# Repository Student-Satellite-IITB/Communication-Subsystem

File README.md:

# Communication-Subsystem
This repository contains all codes related to the Communication Subsystem for IITBSSP CubeSat Mission

Current status: 
- Literature Review
- Link Budget Analysis

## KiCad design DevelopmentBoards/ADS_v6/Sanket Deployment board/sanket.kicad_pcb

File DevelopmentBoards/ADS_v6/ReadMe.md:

# This is work in progress

This folder contains files related to the ADS.

ADS consists of two parts:
1. Sanket Deployment Board
2. Resistor Board

The Sanket Deployment Board contains the files of the main board which houses the regulators for heating nichrome. The Resistor board is a small vertical board that holds the nichrome wires and detector switches.

# Changes in v6 over v5
- The burnwires are in series now to prevent excess current
- The R6 can connect the EN to the voltage regulator directly, enabling easy bypassing of the current limiter

# Errata
- The R12 of the Deployment board (ILIM resistor) should be around 90 kOhm.

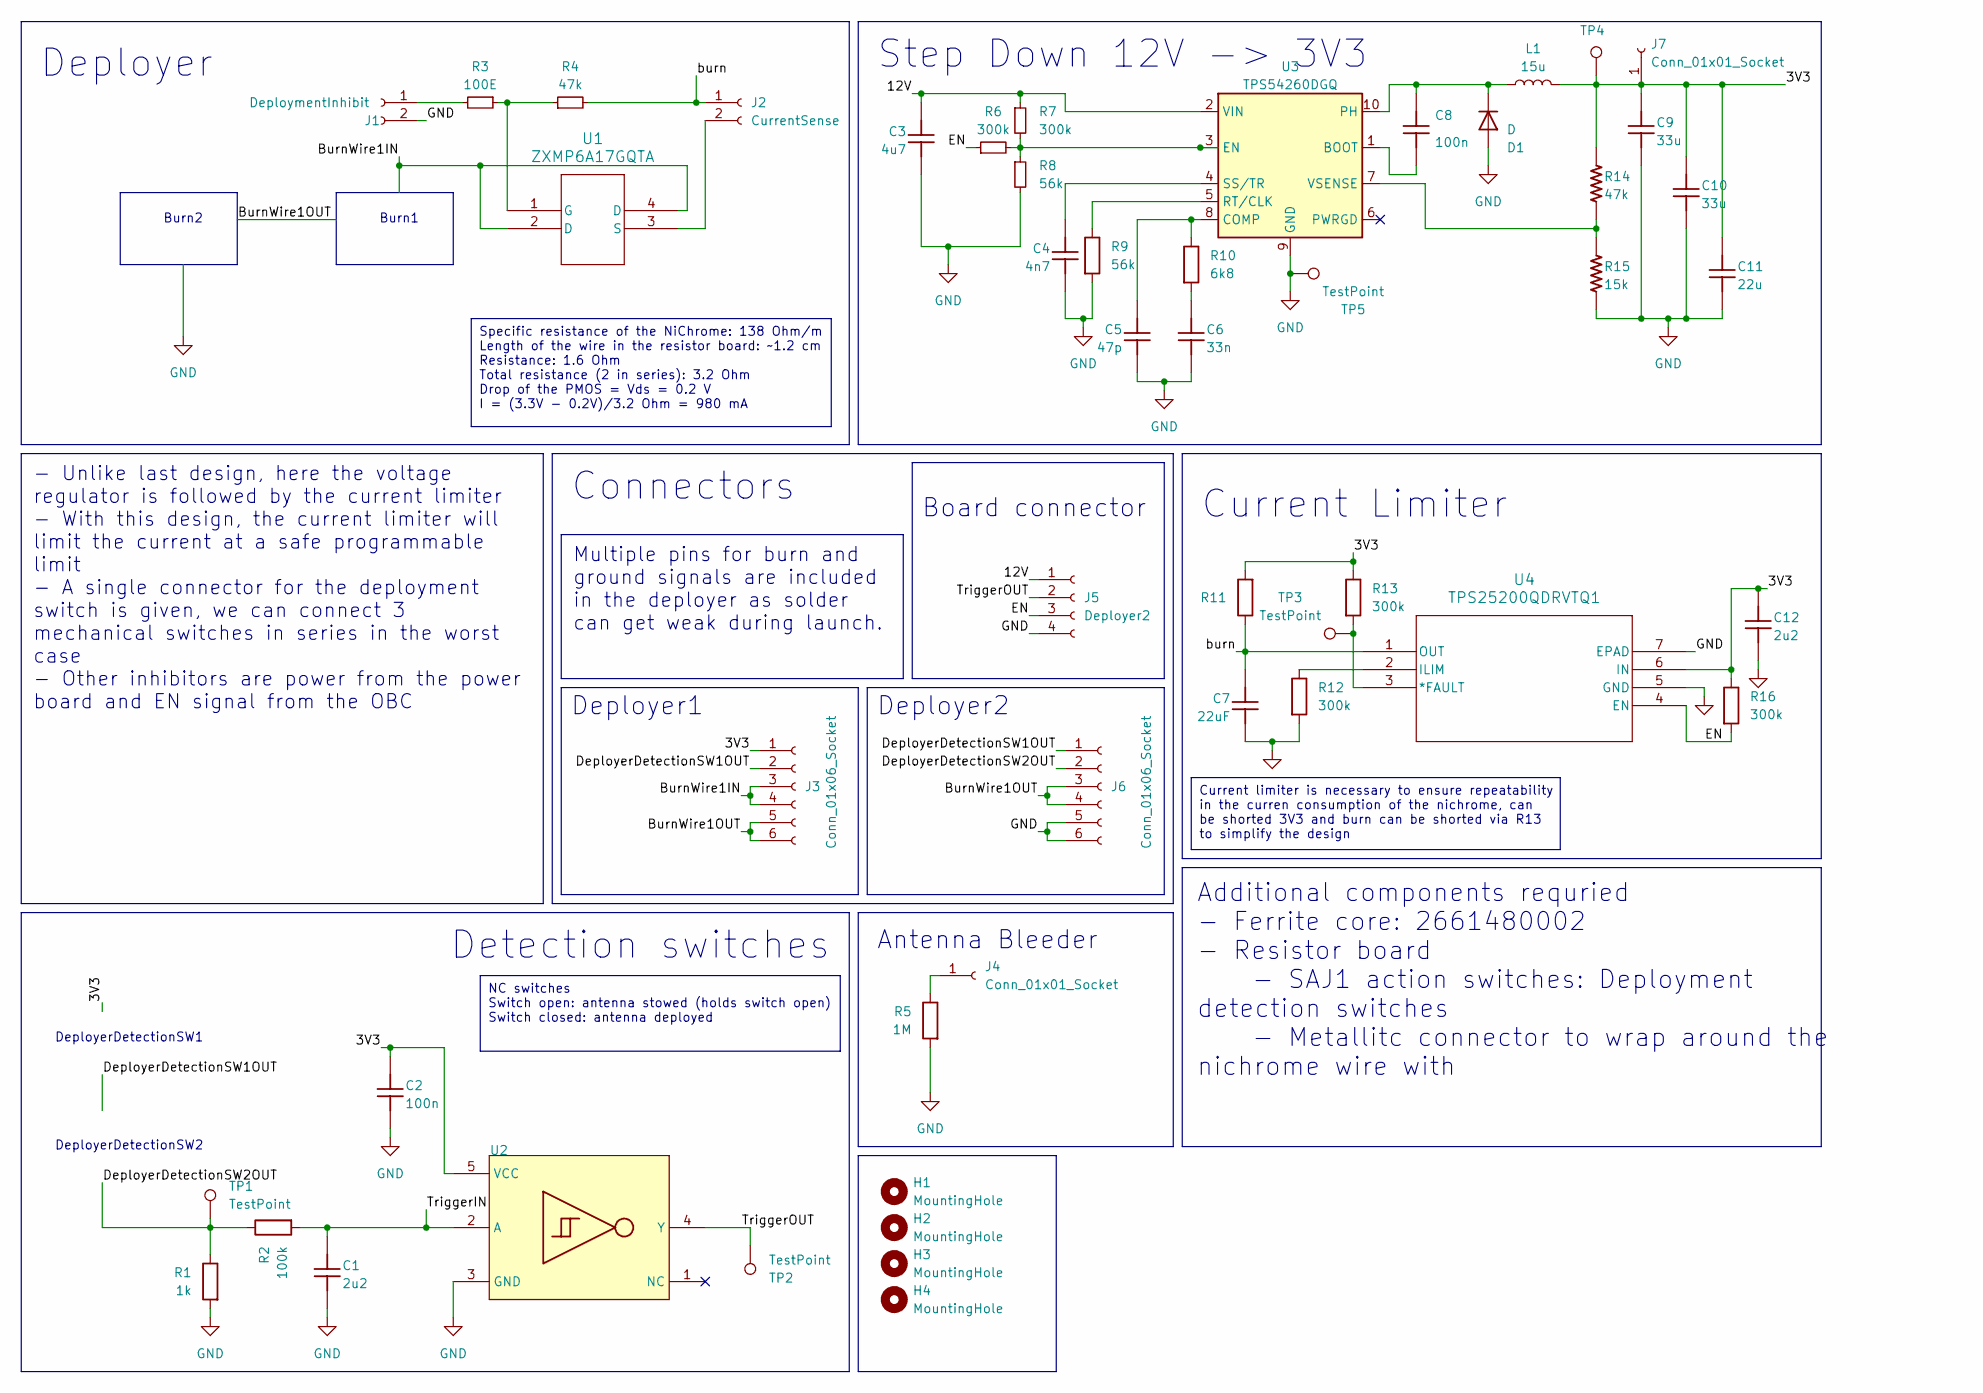
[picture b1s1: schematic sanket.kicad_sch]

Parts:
C1, C12: 2u2; C_0805_2012Metric
C2: 100n; C_0805_2012Metric
C3: 4u7; C_0805_2012Metric; MANUFACTURER PART NUMBER C0603C475K8PACTU
C4: 4n7; C_0805_2012Metric; MANUFACTURER PART NUMBER C0603C475K8PACTU
C5: 47p; C_0805_2012Metric; MANUFACTURER PART NUMBER C0603C475K8PACTU
C6: 33n; C_0805_2012Metric; MANUFACTURER PART NUMBER C0603C475K8PACTU
C7: 22uF; C_0805_2012Metric
C8: 100n; C_0805_2012Metric; MANUFACTURER PART NUMBER C0603C475K8PACTU
C9, C10: 33u; C_1206_3216Metric; MANUFACTURER PART NUMBER C0603C475K8PACTU
C11: 22u; C_0805_2012Metric; MANUFACTURER PART NUMBER C0603C475K8PACTU
D1: D; D_SMA-SMB_Universal_Handsoldering
H1, H2, H3, H4: MountingHole; MountingHole_3.2mm_M3
J1: DeploymentInhibit; PinHeader_1x02_P2.54mm_Vertical
J2: CurrentSense; PinHeader_1x02_P2.54mm_Vertical
J3, J6: Conn_01x06_Socket; PinHeader_1x06_P2.54mm_Vertical
J4, J7: Conn_01x01_Socket; PinSocket_1x01_P2.54mm_Vertical
J5: Deployer2; PinHeader_1x04_P2.54mm_Vertical
L1: 15u; L_Wurth_WE-XHMI-5050
R1: 1k; R_0805_2012Metric
R2: 100k; R_0805_2012Metric
R3: 100E; C_0805_2012Metric
R4, R14: 47k; C_0805_2012Metric
R5: 1M; R_0805_2012Metric
R6, R7: 300k; C_0805_2012Metric
R8: 56k; C_0805_2012Metric
R9: 56k; R_0805_2012Metric
R10: 6k8; R_0805_2012Metric
R11: 300k; C_0603_1608Metric
R12, R13, R16: 300k; R_0805_2012Metric
R15: 15k; C_0805_2012Metric
TP1, TP2, TP3, TP4, TP5: TestPoint; TestPoint_THTPad_1.0x1.0mm_Drill0.5mm
U1: ZXMP6A17GQTA; SOT-223_DIO
U2: SN74LVC1G17QDCKRQ1; SOT-353_SC-70-5
U3: TPS54260DGQ; HVSSOP-10-1EP_3x3mm_P0.5mm_EP1.57x1.88mm
U4: TPS25200QDRVTQ1; WSON-6-1EP_2x2mm_P0.65mm_EP1x1.6mm

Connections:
/3V3: C2.2, C9.2, C10.2, C11.2, C12.2, J3.1, J7.1, L1.2, R11.2, R13.1, R14.1, R16.1, TP4.1, U2.5 (VCC), U4.6 (IN)
/12V: C3.2, J5.1, R7.1, U3.2 (VIN)
/BurnWire1IN: J3.3, J3.4, U1.2 (D), U1.4 (D)
/BurnWire1OUT: J3.5, J3.6, J6.3, J6.4
/DeployerDetectionSW1OUT: J3.2, J6.1
/DeployerDetectionSW2OUT: J6.2, R1.1, R2.1, TP1.1
/EN: J5.3, R6.1, R16.2, U4.4 (EN)
/TriggerIN: C1.2, R2.2, U2.2 (A)
/TriggerOUT: J5.2, TP2.1, U2.4 (Y)
/burn: C7.2, J2.1, R4.2, R11.1, U4.1 (OUT)
GND: C1.1, C2.1, C3.1, C4.1, C5.1, C6.1, C7.1, C9.1, C10.1, C11.1, C12.1, D1.2 (A), J1.2, J5.4, J6.5, J6.6, R1.2, R5.2, R8.2, R9.2, R12.2, R15.2, TP5.1, U2.3 (GND), U3.9 (GND), U3.11 (GND), U4.5 (GND), U4.7 (EPAD)
unnamed: C6.2, R10.2
unnamed: C8.2, D1.1 (K), L1.1, U3.10 (PH)
unnamed: J1.1, R3.2
unnamed: J2.2, U1.3 (S)
unnamed: J4.1, R5.1
unnamed: R3.1, R4.1, U1.1 (G)
unnamed: C8.1, U3.1 (BOOT)
unnamed: C5.2, R10.1, U3.8 (COMP)
unnamed: R6.2, R7.2, R8.1, U3.3 (EN)
unnamed: R9.1, U3.5 (RT/CLK)
unnamed: C4.2, U3.4 (SS/TR)
unnamed: R14.2, R15.1, U3.7 (VSENSE)
unnamed: R13.2, TP3.1, U4.3 (*FAULT)
unnamed: R12.1, U4.2 (ILIM)

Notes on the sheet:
Multiple pins for burn and ground signals are included in the deployer as solder can get weak during launch.
NC switches Switch open: antenna stowed (holds switch open) Switch closed: antenna deployed
- Unlike last design, here the voltage regulator is followed by the current limiter - With this design, the current limiter will limit the current at a safe programmable limit - A single connector for the deployment switch is given, we can connect 3 mechanical switches in series in the worst case -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
Additional components requried - Ferrite core: 2661480002 - Resistor board - SAJ1 action switches: Deployment detection switches - Metallitc connector to wrap around the nichrome wire with
Current limiter is necessary to ensure repeatability in the curren consumption of the nichrome, can be shorted 3V3 and burn can be shorted via R13 to simplify the design
Specific resistance of the NiChrome: 138 Ohm/m Length of the wire in the resistor board: ~1.2 cm Resistance: 1.6 Ohm Total resistance (2 in series): 3.2 Ohm Drop of the PMOS = Vds = 0.2 V I = (3.3V - 0.2V)/3.2 Ohm = 980 mA
Step Down 12V -> 3V3
Detection switches
Connectors
Board connector
Deployer
Burn1
DeployerDetectionSW1
Deployer2
Current Limiter
Deployer1
DeployerDetectionSW2
Burn2
Antenna Bleeder

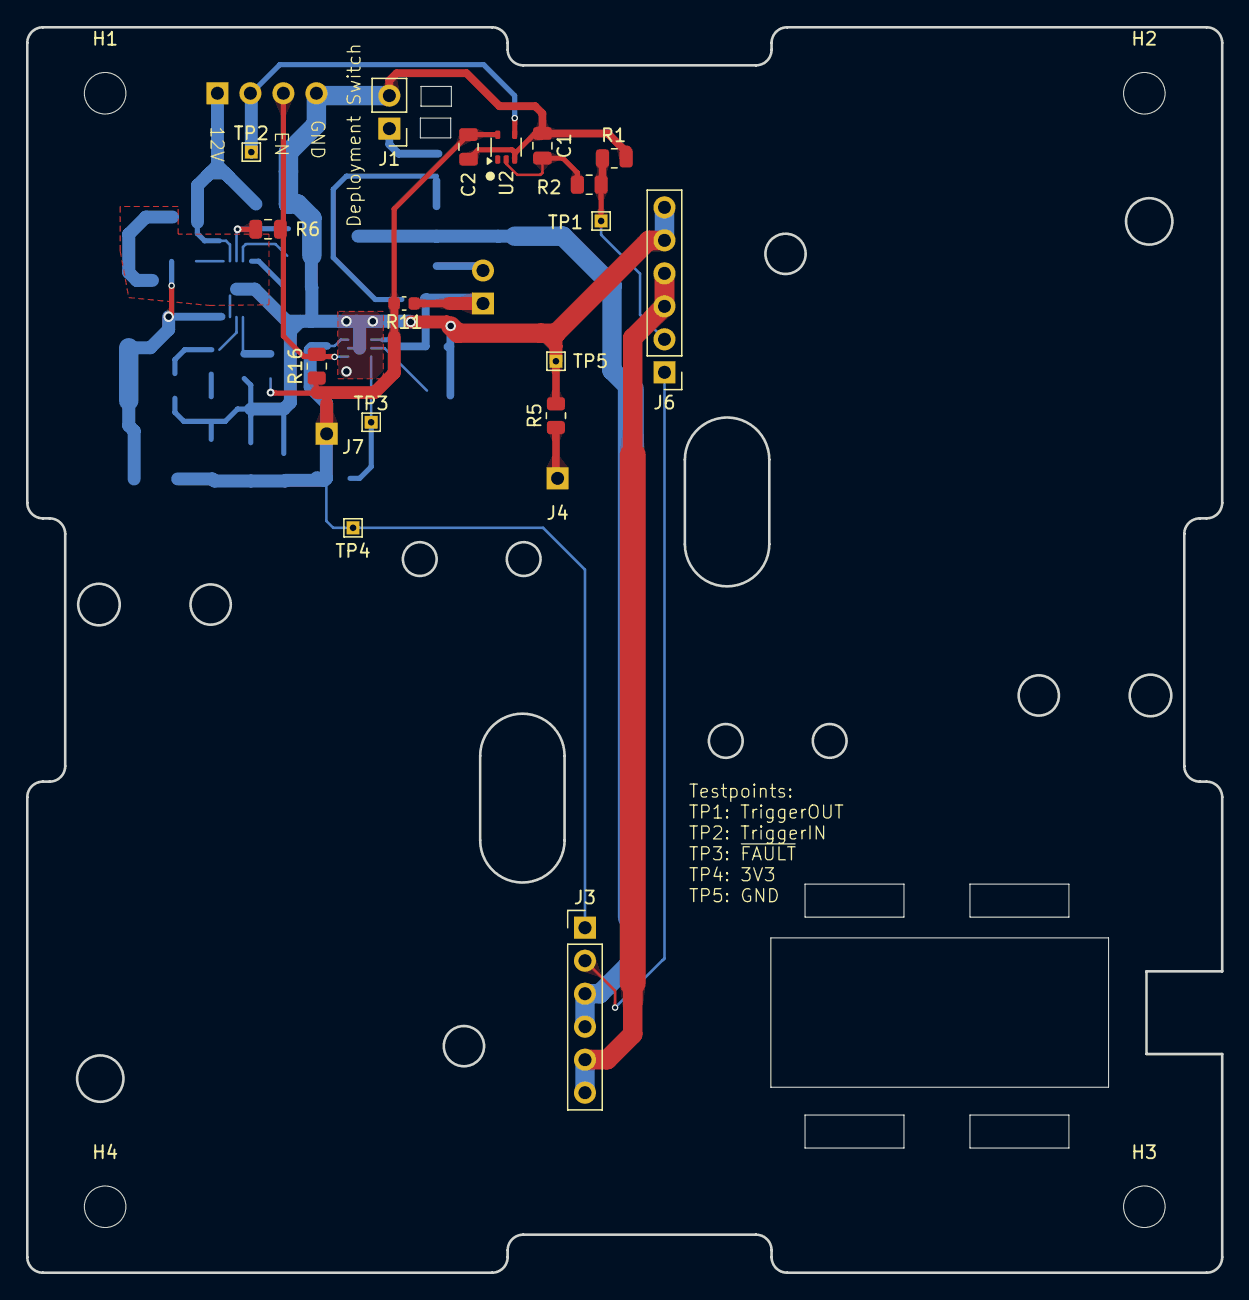
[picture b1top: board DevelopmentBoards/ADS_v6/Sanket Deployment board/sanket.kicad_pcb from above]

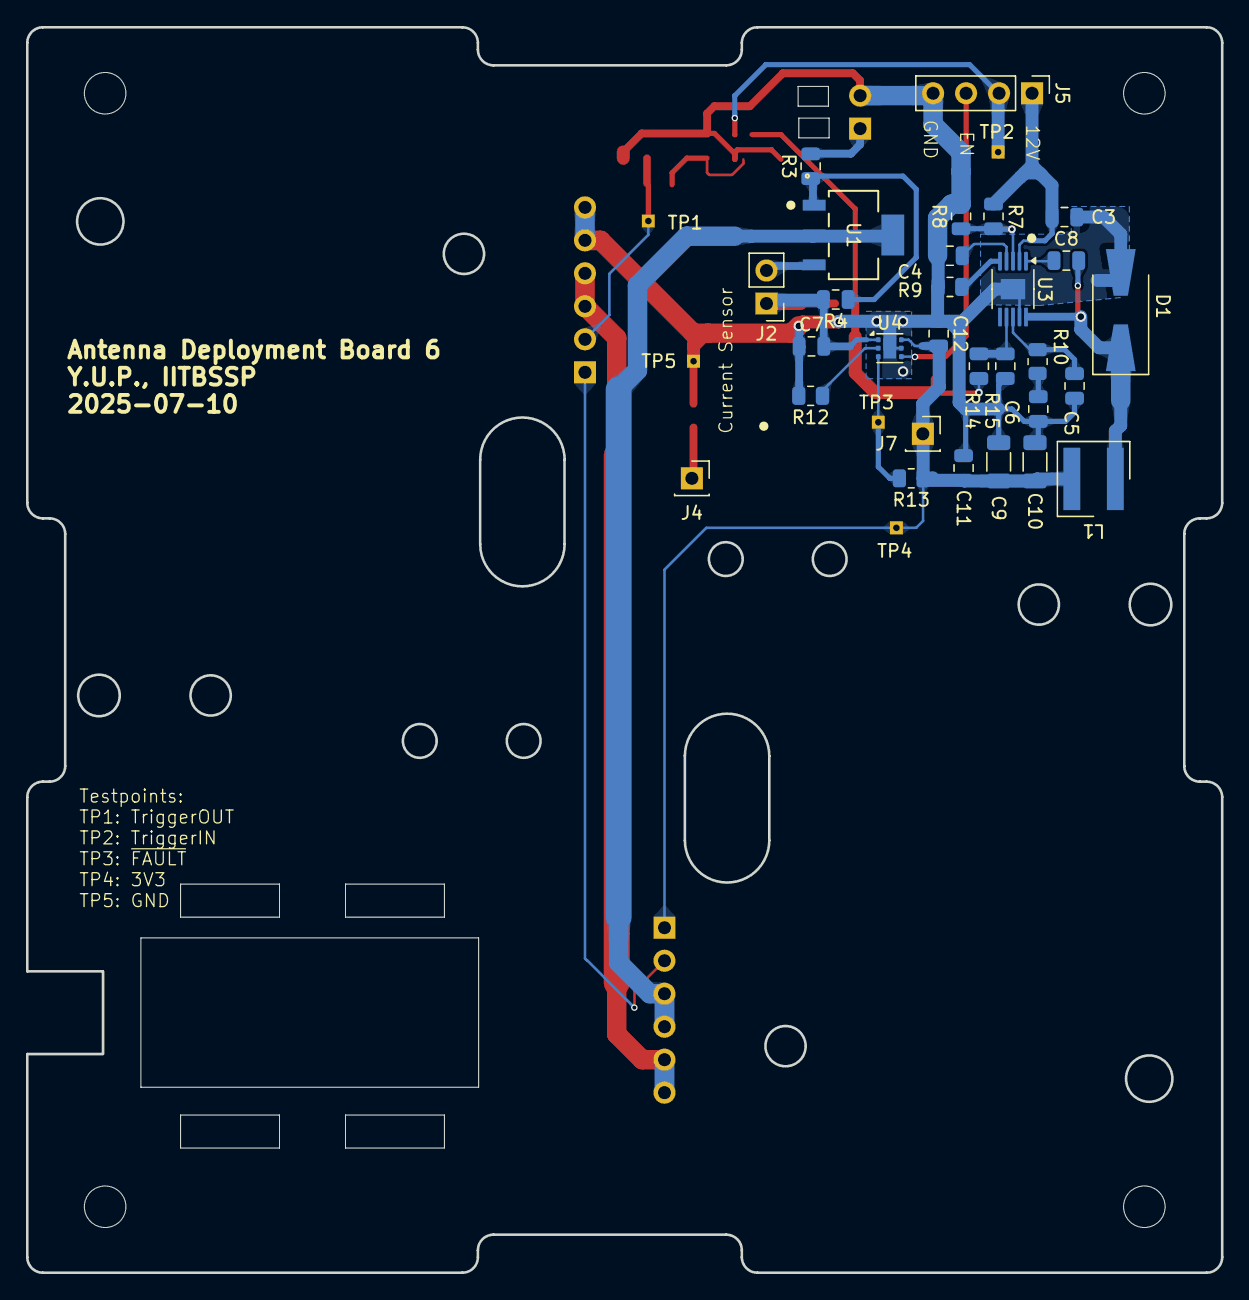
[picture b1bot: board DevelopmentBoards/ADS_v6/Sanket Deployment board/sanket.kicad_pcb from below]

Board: 2 copper layers, 92.0 x 95.9 mm, 50 parts (29 on the bottom side), 25 nets.

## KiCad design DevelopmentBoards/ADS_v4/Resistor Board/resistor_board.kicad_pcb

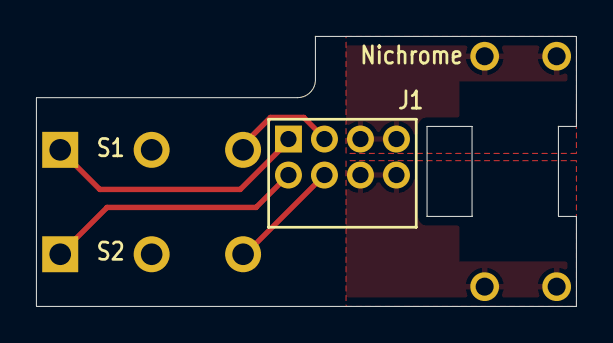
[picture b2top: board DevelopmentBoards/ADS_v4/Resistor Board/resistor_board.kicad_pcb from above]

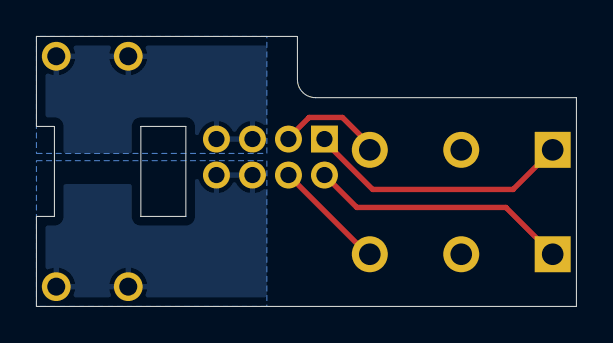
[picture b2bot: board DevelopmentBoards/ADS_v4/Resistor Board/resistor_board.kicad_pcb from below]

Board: 4 copper layers, 30.0 x 15.0 mm, 5 parts (2 on the bottom side), 6 nets.

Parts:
J1: TMM-104-01-X-D-RA
Nichrome: UB3C
R2: UB3C
S1, S2: D2F-L

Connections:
R_HI: J1.6, J1.8, Nichrome.2, R2.2
R_LO: J1.5, J1.7, Nichrome.1, R2.1
S1_COM: J1.1, S1.1
S1_NC: J1.3, S1.2
S2_COM: J1.2, S2.1
S2_NC: J1.4, S2.2

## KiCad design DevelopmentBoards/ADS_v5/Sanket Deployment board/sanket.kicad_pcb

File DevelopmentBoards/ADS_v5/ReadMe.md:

This folder contains files related to the ADS.

ADS consists of two parts:
1. Sanket Deployment Board
2. Resistor Board

The Sanket Deployment Board contains the files of the main board which houses the regulators for heating nichrome. The Resistor board is a small vertical board which hold the nichrome wires and detector switches.

# Changes in v5 over v4
- Constant voltage regulator as opposed to the adjustable voltage
- Current limiter supplies nichrome as opposed to voltage regulator
- Number of pin changed in supply diagram
- Board now accepts 12V
- Deployment switch added
- Number of pins on the resistor board changed, now in a 6 pins single row
- Traces are now extra wide (7.2 mm → 1.5 mm)
- Added an extra cut to accomodate the coaxial cable

# Improvements needed in v5
- The TPS25200 enable high means the current is disables
- If the nicrhome wires are used in series, current limiter can be eliminated
- There is no compensation network on the switching converter (F)

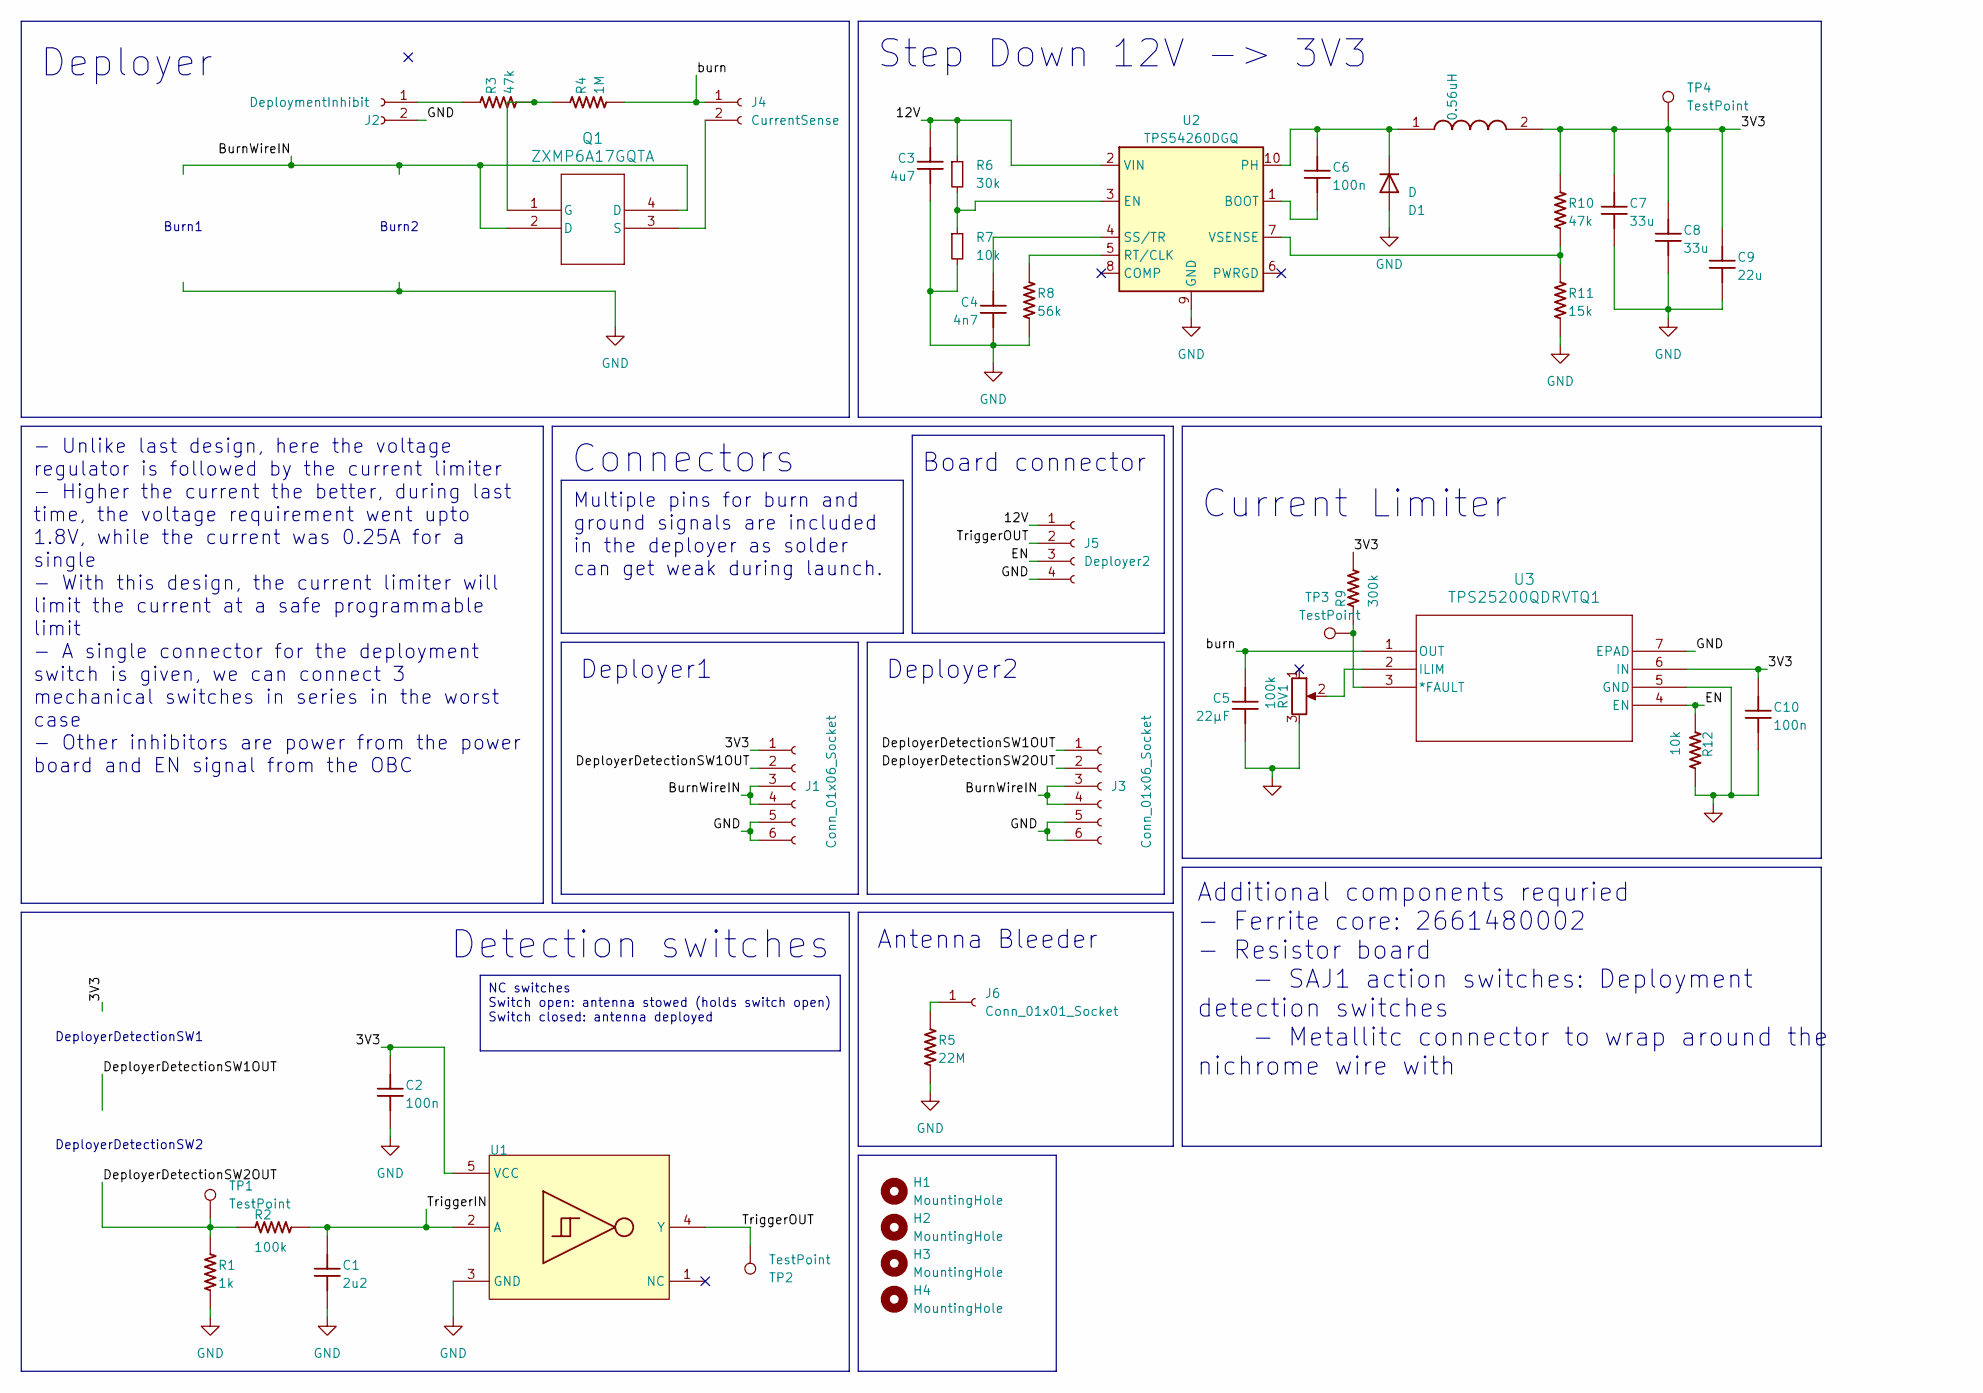
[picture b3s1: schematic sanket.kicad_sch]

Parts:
C1: 2u2; C_0805_2012Metric
C2, C10: 100n; C_0805_2012Metric
C3: 4u7; C_0805_2012Metric; MANUFACTURER PART NUMBER C0603C475K8PACTU
C4: 4n7; C_0805_2012Metric; MANUFACTURER PART NUMBER C0603C475K8PACTU
C5: 22µF; C_0805_2012Metric
C6: 100n; C_0805_2012Metric; MANUFACTURER PART NUMBER C0603C475K8PACTU
C7, C8: 33u; C_1206_3216Metric; MANUFACTURER PART NUMBER C0603C475K8PACTU
C9: 22u; C_0805_2012Metric; MANUFACTURER PART NUMBER C0603C475K8PACTU
D1: D; D_SMA-SMB_Universal_Handsoldering
H1, H2, H3, H4: MountingHole; MountingHole_3.2mm_M3
J1, J3: Conn_01x06_Socket; PinHeader_1x06_P2.54mm_Vertical
J2: DeploymentInhibit; PinHeader_1x02_P2.54mm_Vertical
J4: CurrentSense; PinHeader_1x02_P2.54mm_Vertical
J5: Deployer2; PinHeader_1x04_P2.54mm_Vertical
J6: Conn_01x01_Socket; PinSocket_1x01_P2.54mm_Vertical
L1: 0.56uH; L_Bourns_SRP5030T; Manufacturer_Part_Number SRP5030CA-R56M
Q1: ZXMP6A17GQTA; SOT-223_DIO
R1: 1k; R_0805_2012Metric
R2: 100k; R_0805_2012Metric; MANUFACTURER PART NUMBER ERJ3EKF1003V
R3, R10: 47k; C_0805_2012Metric
R4: 1M; R_0805_2012Metric
R5: 22M; C_0805_2012Metric
R6: 30k; C_0805_2012Metric
R7, R12: 10k; C_0805_2012Metric
R8: 56k; C_0805_2012Metric
R9: 300k; C_0805_2012Metric
R11: 15k; C_0805_2012Metric
RV1: 100k; Potentiometer_Bourns_3314G_Vertical
TP1, TP2, TP3, TP4: TestPoint; TestPoint_THTPad_1.0x1.0mm_Drill0.5mm
U1: SN74LVC1G17QDCKRQ1; SOT-353_SC-70-5
U2: TPS54260DGQ; HVSSOP-10-1EP_3x3mm_P0.5mm_EP1.57x1.88mm
U3: TPS25200QDRVTQ1; WSON-6-1EP_2x2mm_P0.65mm_EP1x1.6mm

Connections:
/3V3: C2.2, C7.2, C8.2, C9.2, C10.2, J1.1, L1.2, R9.2, R10.1, TP4.1, U1.5 (VCC), U3.6 (IN)
/12V: C3.2, J5.1, R6.1, U2.2 (VIN)
/BurnWireIN: J1.3, J1.4, J3.3, J3.4, Q1.2 (D), Q1.4 (D)
/DeployerDetectionSW1OUT: J1.2, J3.1
/DeployerDetectionSW2OUT: J3.2, R1.2, R2.1, TP1.1
/EN: J5.3, R12.1, U3.4 (EN)
/TriggerIN: C1.2, R2.2, U1.2 (A)
/TriggerOUT: J5.2, TP2.1, U1.4 (Y)
/burn: C5.2, J4.1, R4.2, U3.1 (OUT)
GND: C1.1, C2.1, C3.1, C4.1, C5.1, C7.1, C8.1, C9.1, C10.1, D1.2 (A), J1.5, J1.6, J2.2, J3.5, J3.6, J5.4, R1.1, R5.2, R7.2, R8.2, R11.2, R12.2, RV1.3, U1.3 (GND), U2.9 (GND), U2.11 (GND), U3.5 (GND), U3.7 (EPAD)
unnamed: C6.2, D1.1 (K), L1.1, U2.10 (PH)
unnamed: J2.1, R3.1
unnamed: J4.2, Q1.3 (S)
unnamed: J6.1, R5.1
unnamed: Q1.1 (G), R3.2, R4.1
unnamed: C6.1, U2.1 (BOOT)
unnamed: R6.2, R7.1, U2.3 (EN)
unnamed: R8.1, U2.5 (RT/CLK)
unnamed: C4.2, U2.4 (SS/TR)
unnamed: R10.2, R11.1, U2.7 (VSENSE)
unnamed: R9.1, TP3.1, U3.3 (*FAULT)
unnamed: RV1.2, U3.2 (ILIM)

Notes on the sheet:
Multiple pins for burn and ground signals are included in the deployer as solder can get weak during launch.
NC switches Switch open: antenna stowed (holds switch open) Switch closed: antenna deployed
- Unlike last design, here the voltage regulator is followed by the current limiter - Higher the current the better, during last time, the voltage requirement went upto 1.8V, while the current was 0.25A for a single - With this design, the current limiter will limit the current at a safe programmab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
Additional components requried - Ferrite core: 2661480002 - Resistor board - SAJ1 action switches: Deployment detection switches - Metallitc connector to wrap around the nichrome wire with
Step Down 12V -> 3V3
Detection switches
Connectors
Board connector
Deployer
Burn2
Burn1
DeployerDetectionSW1
Deployer2
Current Limiter
Deployer1
DeployerDetectionSW2
Antenna Bleeder

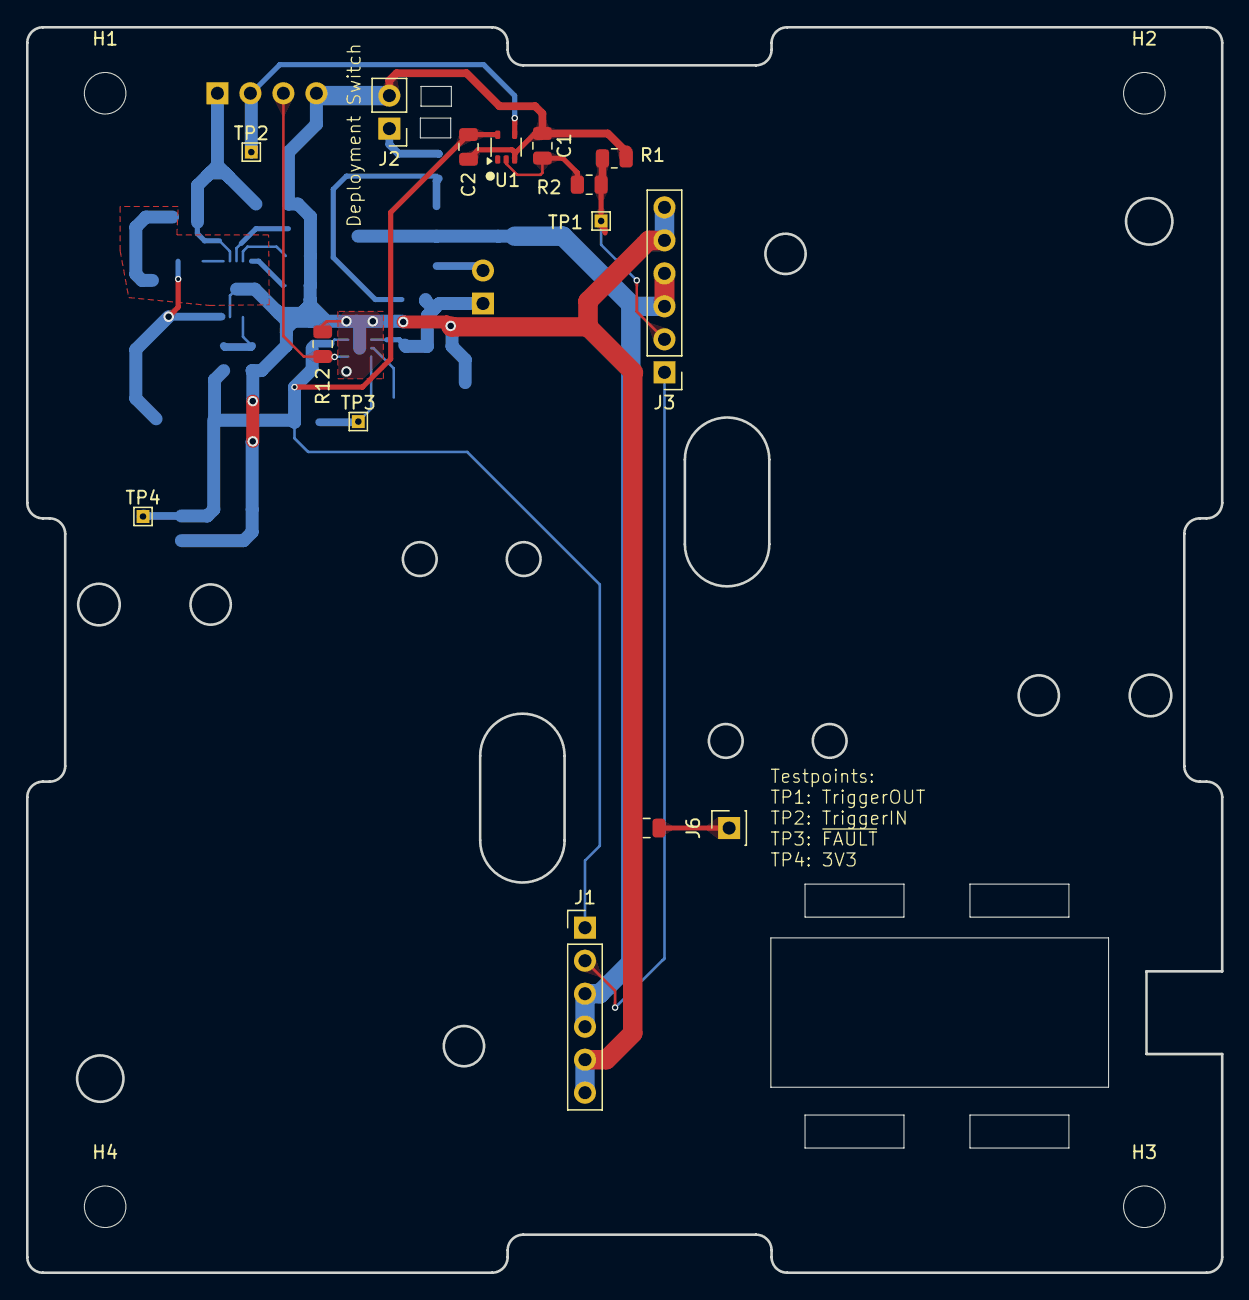
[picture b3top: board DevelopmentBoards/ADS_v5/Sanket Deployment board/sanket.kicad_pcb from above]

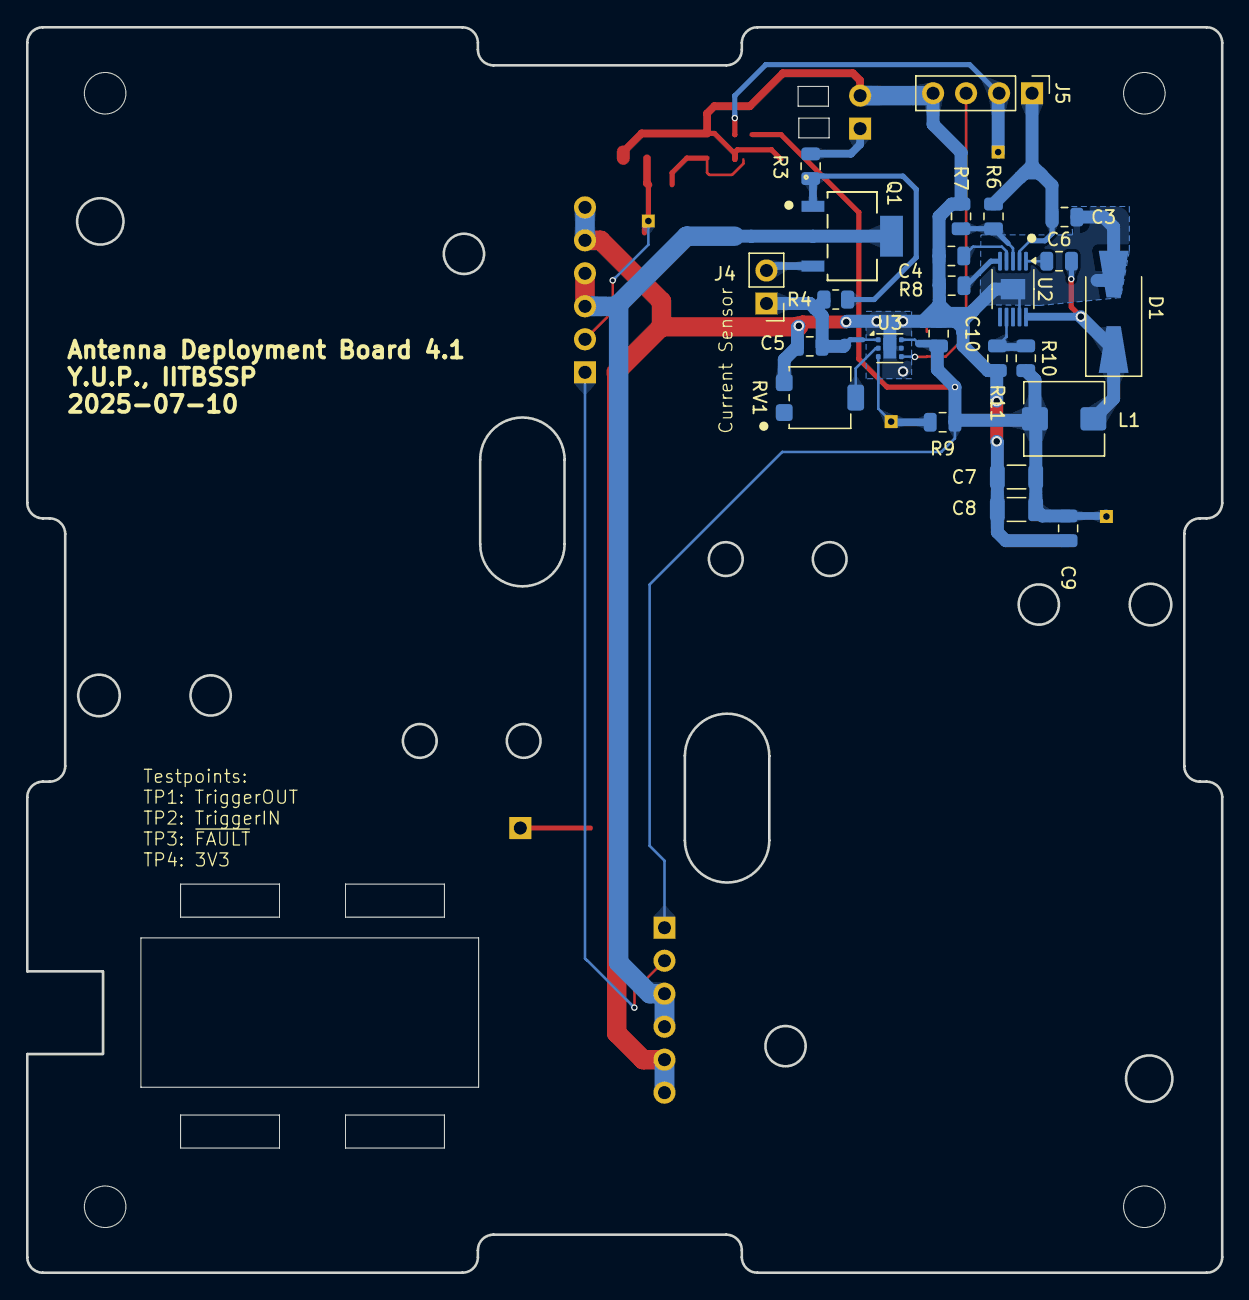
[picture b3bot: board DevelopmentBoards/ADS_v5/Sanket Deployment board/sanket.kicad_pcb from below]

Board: 2 copper layers, 92.0 x 95.9 mm, 43 parts (24 on the bottom side), 22 nets.

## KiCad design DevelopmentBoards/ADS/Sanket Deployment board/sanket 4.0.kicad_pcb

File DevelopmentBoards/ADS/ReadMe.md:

This folder contains files related to the ADS.

ADS consists of two parts:
1. Sanket Deployment Board
2. Resistor Board

The Sanket Deployment Board contains the files of the main board which houses the regulators for heating nichrome. The Resistor board is a small vertical board which hold the nichrome wires and detector switches.

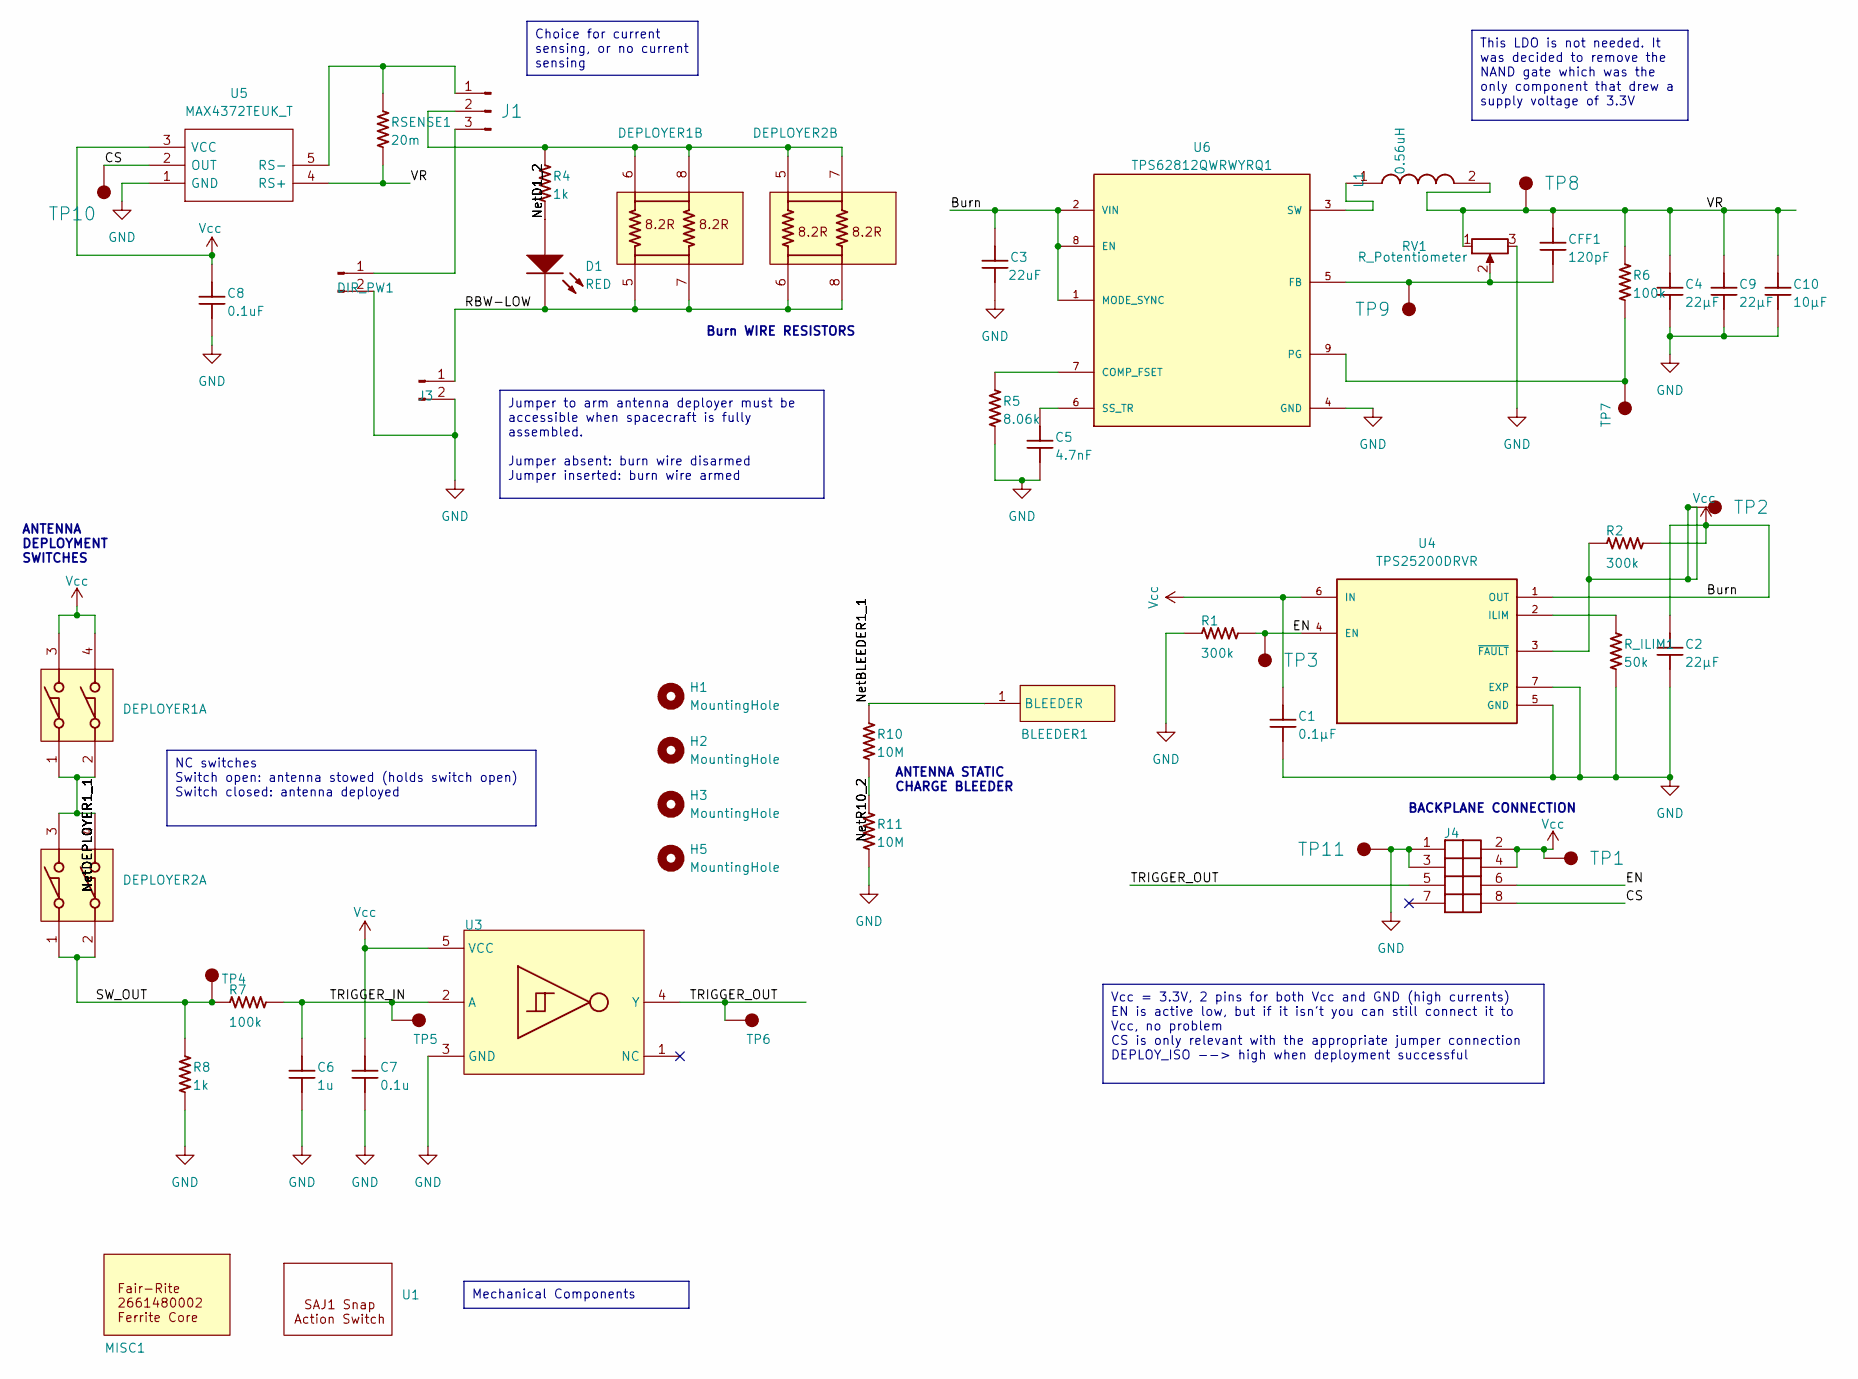
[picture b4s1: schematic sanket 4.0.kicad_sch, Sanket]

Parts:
BLEEDER1: Present (no need to buy); MISC-BLEEDER-PAD
C1: 0.1µF; CAP-0603-KEMET
C2: 22µF; CAP-0603-KEMET
C3: 22uF; CAP-0603-KEMET; MANUFACTURER PART NUMBER C0603C475K8PACTU
C4, C9: 22µF; CAP-0603-KEMET; MANUFACTURER PART NUMBER C0603C475K8PACTU
C5: 4.7nF; CAP-0603-KEMET; MANUFACTURER PART NUMBER C0603C475K8PACTU
C6: 1u; CAP-0603-KEMET
C7: 0.1u; CAP-0603-KEMET
C8: 0.1uF; CAP-0603-KEMET
C10: 10µF; CAP-0603-KEMET; MANUFACTURER PART NUMBER C0603C475K8PACTU
CFF1: 120pF; CAP-0603-KEMET; MANUFACTURER PART NUMBER C0603C475K8PACTU
D1: RED; LED_0603_150060RS75000
DEPLOYER1: MECH-Deployer-Shield
DEPLOYER2: MECH-DEPLOYER-CENTRE
DIR_PW1: ARM_Header; PinHeader_1x02_P2.54mm_Vertical
H1, H2, H3, H5: MountingHole; MountingHole_3.2mm_M3
J1: HEAD-RA-SMT-2.54mm-1x3; PinHeader_1x03_P2.54mm_Vertical; Manufacturer Part Number M20-8890345
J3: ARM_Header; PinHeader_1x02_P2.54mm_Vertical
J4: Backplane; HEAD_TSW-104-14-L-D
L1: 0.56uH; L_Bourns_SRP5030T; Manufacturer_Part_Number SRP5030CA-R56M
MISC1: Ferrite bead; MISC-FERRITE-2661480002
R1, R2: 300k; RES_0603_Panasonic
R4, R8: 1k; RES_0603_Panasonic
R5: 8.06k; RES_0603_Panasonic
R6: 100k; RES_0603_Panasonic
R7: 100k; RES_0603_Panasonic; MANUFACTURER PART NUMBER ERJ3EKF1003V
R10, R11: 10M; RES_0603_Panasonic
RSENSE1: 20m; RES_0603_Panasonic
RV1: R_Potentiometer; Potentiometer_Runtron_RM-065_Vertical
R_ILIM1: 50k; RES_0603_Panasonic
TP1, TP2, TP3, TP4, TP5, TP6, TP7, TP8, TP9, TP10, TP11: Test points; MISC-TP-SURF
U1: (no value)
U3: SN74LVC1G17QDCKRQ1; IC_SC70-5
U4: TPS25200DRVR; SON65P200X200X80-7N; PARTREV D; DigiKey_Part_Number 296-37842-2-ND
U5: MAX4372TEUK_T; SOT95P280X145-5N; MPN MAX4372TEUK+T; DigiKey_Part_Number MAX4372TEUK+TTR-ND
U6: TPS62812QWRWYRQ1; RWY0009A; MANUFACTURER_PART_NUMBER TPS62812QWRWYRQ1

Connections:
/CS: J4.8, TP10.1, U5.2 (OUT)
/EN: J4.6, R1.2, TP3.1, U4.4 (EN)
/NetBLEEDER1_1: BLEEDER1.1 (BLEEDER), R10.1
/NetD1_2: D1.2 (A), R4.1
/NetDEPLOYER1_1: DEPLOYER1.1, DEPLOYER1.2, DEPLOYER2.3, DEPLOYER2.4
/NetR10_2: R10.2, R11.1
/RBW-LOW: D1.1 (K), DEPLOYER1.5, DEPLOYER1.7, DEPLOYER2.6, DEPLOYER2.8, J3.1
/SW_OUT: DEPLOYER2.1, DEPLOYER2.2, R7.1, R8.2, TP4.1
/TRIGGER_IN: C6.2, R7.2, TP5.1, U3.2 (A)
/TRIGGER_OUT: J4.5, TP6.1, U3.4 (Y)
/VR: C4.2, C9.2, C10.2, CFF1.2, L1.2, R6.1, RSENSE1.1, RV1.1, TP8.1, U5.4 (RS+)
GND: C1.1, C2.1, C3.1, C4.1, C5.1, C6.1, C7.1, C8.1, C9.1, C10.1, DIR_PW1.2, J3.2, J4.1, J4.3, R1.1, R5.2, R8.1, R11.2, RV1.3, R_ILIM1.2, TP11.1, U3.3 (GND), U4.5 (GND), U4.7 (EXP), U5.1 (GND), U6.4 (GND)
unnamed: DIR_PW1.1, J1.3
unnamed: J1.1, RSENSE1.2, U5.5 (RS-)
unnamed: DEPLOYER1.6, DEPLOYER1.8, DEPLOYER2.5, DEPLOYER2.7, J1.2, R4.2
unnamed: R_ILIM1.1, U4.2 (ILIM)
unnamed: R2.1, TP2.1, U4.3 (~FAULT)
unnamed: R5.1, U6.7 (COMP_FSET)
unnamed: CFF1.1, RV1.2, TP9.1, U6.5 (FB)
unnamed: R6.2, TP7.1, U6.9 (PG)
unnamed: C5.2, U6.6 (SS_TR)
unnamed: L1.1, U6.3 (SW)

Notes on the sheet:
ANTENNA STATIC CHARGE BLEEDER
This LDO is not needed. It was decided to remove the NAND gate which was the only component that drew a supply voltage of 3.3V
Burn WIRE RESISTORS
Mechanical Components
ANTENNA DEPLOYMENT SWITCHES
NC switches Switch open: antenna stowed (holds switch open) Switch closed: antenna deployed
Vcc = 3.3V, 2 pins for both Vcc and GND (high currents) EN is active low, but if it isn't you can still connect it to Vcc, no problem CS is only relevant with the appropriate jumper connection DEPLOY_ISO --> high when deployment successful
BACKPLANE CONNECTION
Choice for current sensing, or no current sensing
Jumper to arm antenna deployer must be accessible when spacecraft is fully assembled. Jumper absent: burn wire disarmed Jumper inserted: burn wire armed

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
